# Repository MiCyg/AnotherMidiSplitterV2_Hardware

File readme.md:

# Another MIDI Splitter V2 Hardware

[← Back to main repository](https://github.com/MiCyg/AnotherMidiSplitterV2.git)

---

A classic schematic and PCB design for a MIDI splitter. It is powered by a 5V USB-C connector. Contains 8 MIDI outputs on DIN-5 connectors, and in the latest version I added LEDs to check if the PCB works.

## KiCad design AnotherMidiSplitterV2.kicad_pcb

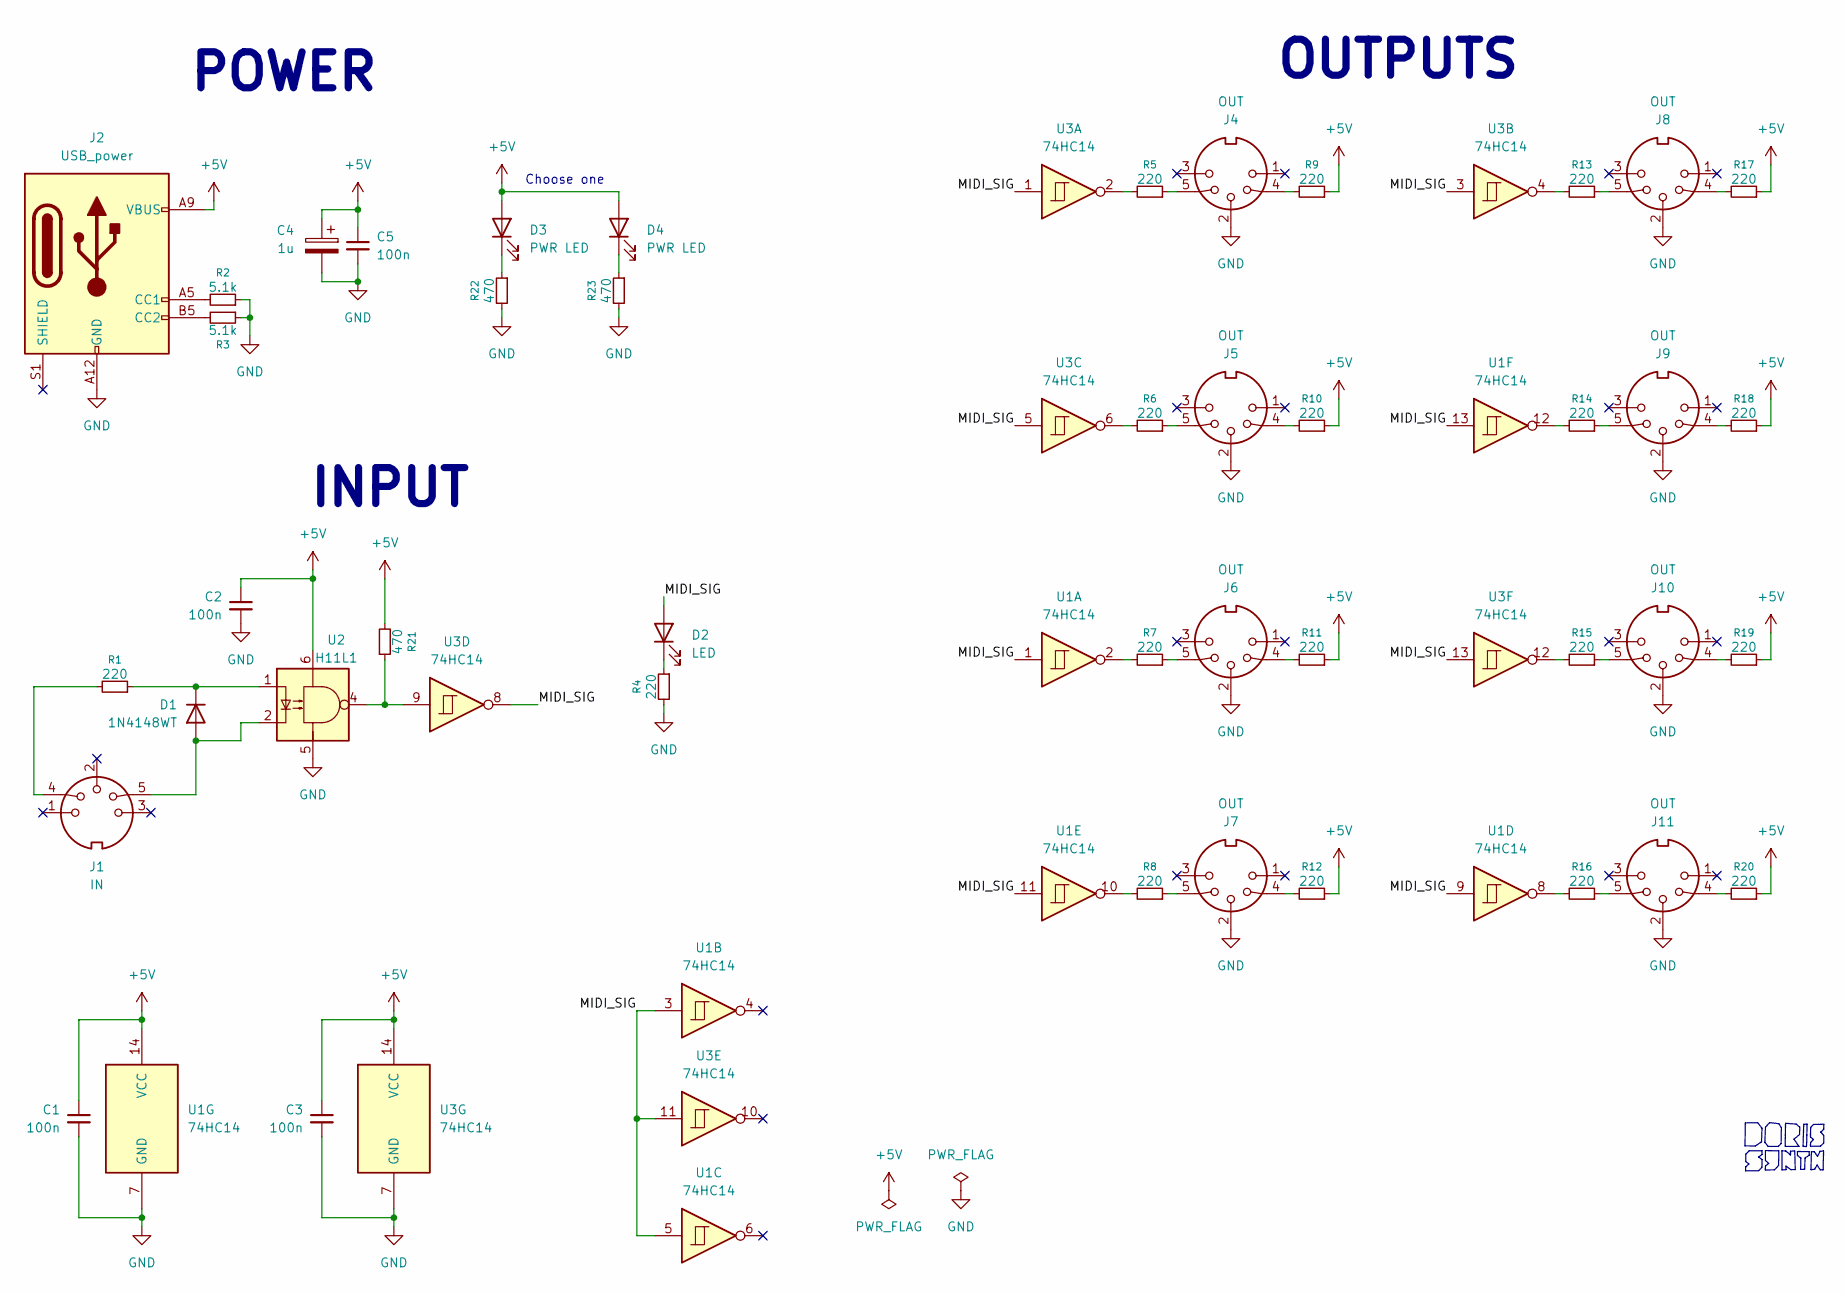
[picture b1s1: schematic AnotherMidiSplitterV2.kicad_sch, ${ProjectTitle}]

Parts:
C1, C2, C3, C5: 100n; C_0805_2012Metric_Pad1.18x1.45mm_HandSolder
C4: 1u; C_0805_2012Metric_Pad1.18x1.45mm_HandSolder
D1: 1N4148WT; D_1206_3216Metric
D2: LED; LED_1206_3216Metric
D3: PWR LED; LED_1206_3216Metric
D4: PWR LED; LED_D3.0mm_Horizontal_O1.27mm_Z2.0mm
J1: IN; MIDI_DIN5
J2: USB_power; USB_C_Receptacle_HRO_TYPE-C-31-M-17
J4, J5, J6, J7, J8, J9, J10, J11: OUT; MIDI_DIN5
R1, R4, R5, R6, R7, R8, R9, R10, R11, R12, R13, R14, R15, R16, R17, R18, R19, R20: 220; R_0603_1608Metric_Pad0.98x0.95mm_HandSolder
R2, R3: 5.1k; R_0603_1608Metric_Pad0.98x0.95mm_HandSolder
R21, R22, R23: 470; R_0603_1608Metric_Pad0.98x0.95mm_HandSolder
U1, U3: 74HC14; SO-14_5.3x10.2mm_P1.27mm
U2: H11L1; DIP-6_W8.89mm_SMDSocket_LongPads

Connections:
+5V: C1.1, C2.1, C3.1, C4.1, C5.1, D3.2 (A), D4.2 (A), J2.A9 (VBUS), J2.B9 (VBUS), R9.1, R10.1, R11.1, R12.1, R17.1, R18.1, R19.1, R20.1, R21.2, U1.14 (VCC), U2.6, U3.14 (VCC)
/MIDI_SIG: D2.2 (A), U1.1, U1.3, U1.5, U1.9, U1.11, U1.13, U3.1, U3.3, U3.5, U3.8, U3.11, U3.13
GND: C1.2, C2.2, C3.2, C4.2, C5.2, J2.A12 (GND), J2.B12 (GND), J4.2, J5.2, J6.2, J7.2, J8.2, J9.2, J10.2, J11.2, R2.1, R3.1, R4.2, R22.2, R23.2, U1.7 (GND), U2.5, U3.7 (GND)
unnamed: D1.2 (A), J1.5, U2.2
unnamed: D1.1 (K), R1.1, U2.1
unnamed: D2.1 (K), R4.1
unnamed: D3.1 (K), R22.1
unnamed: D4.1 (K), R23.1
unnamed: J1.4, R1.2
unnamed: J2.A5 (CC1), R2.2
unnamed: J2.B5 (CC2), R3.2
unnamed: J4.4, R9.2
unnamed: J4.5, R5.1
unnamed: J5.4, R10.2
unnamed: J5.5, R6.1
unnamed: J6.4, R11.2
unnamed: J6.5, R7.1
unnamed: J7.4, R12.2
unnamed: J7.5, R8.1
unnamed: J8.4, R17.2
unnamed: J8.5, R13.1
unnamed: J9.4, R18.2
unnamed: J9.5, R14.1
unnamed: J10.4, R19.2
unnamed: J10.5, R15.1
unnamed: J11.4, R20.2
unnamed: J11.5, R16.1
unnamed: R5.2, U3.2
unnamed: R6.2, U3.6
unnamed: R7.2, U1.2
unnamed: R8.2, U1.10
unnamed: R13.2, U3.4
unnamed: R14.2, U1.12
unnamed: R15.2, U3.12
unnamed: R16.2, U1.8
unnamed: R21.1, U2.4, U3.9

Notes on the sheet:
OUTPUTS
POWER
INPUT
Choose one

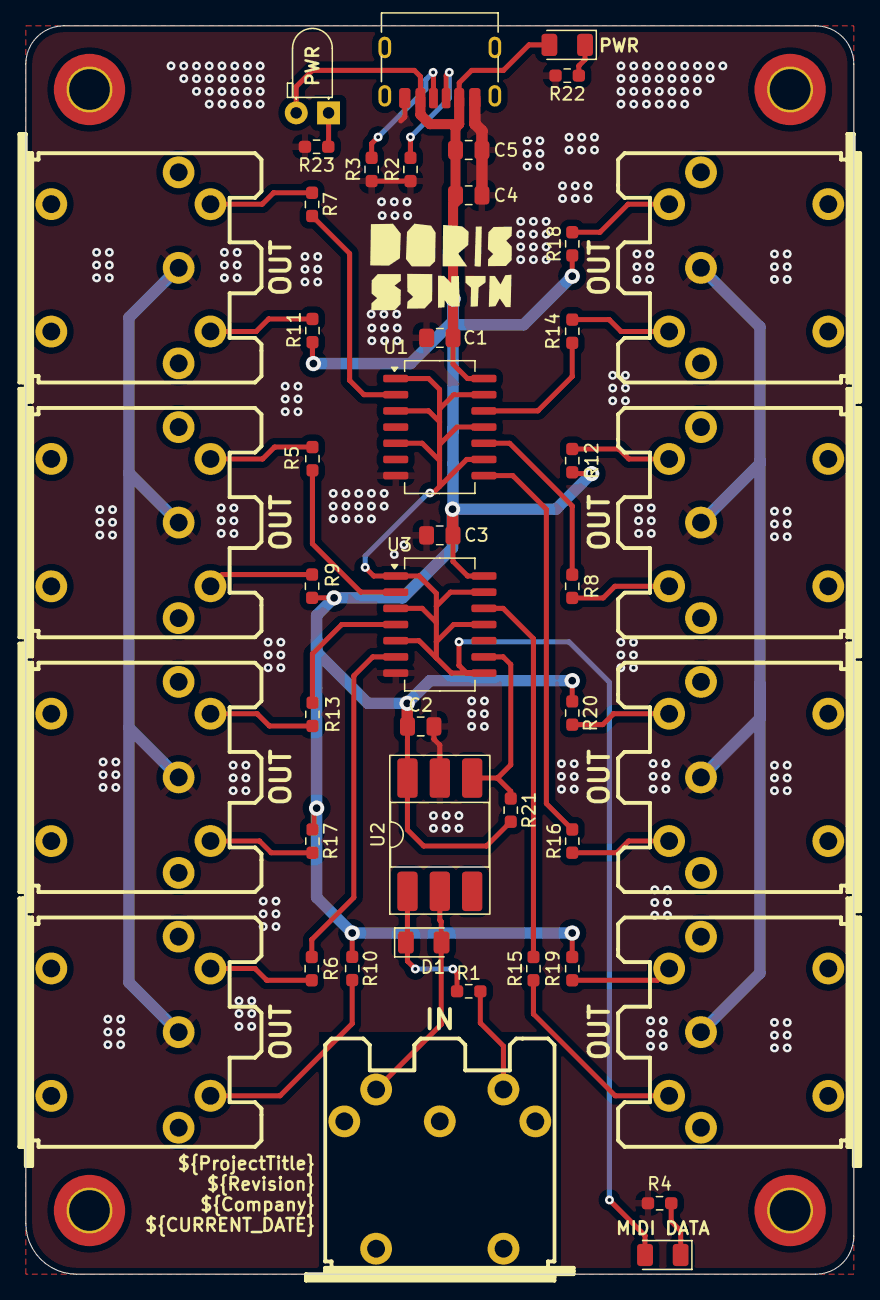
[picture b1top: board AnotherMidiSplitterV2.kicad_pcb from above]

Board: 2 copper layers, 65.0 x 98.0 mm, 45 parts (0 on the bottom side), 36 nets.

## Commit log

2025-10-02 chore: Initial commit - first version of PCB
2025-10-02 chore: add external libraries
2025-10-05 some changes and export 3d model
2025-10-14 change elements to tht update layout
2025-10-23 add resistor to optoisolator
2025-11-05 add logo and some descriptions to schematic, update gitignore
2025-11-23 Update Variables
2026-02-10 doc: Done first version
2026-02-15 Export new version of hardware
